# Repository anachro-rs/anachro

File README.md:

# Anachro Computer

**See [the documentation](https://anachro.computer) for more details!**

## Components

* [Anachro ICD](./crates/icd/README.md) - The Interface Control Document, containing protocol messages used between the Arbitrator/Client.
* [Client](./crates/client/README.md) - The Client Library, intended to run on each client
* [Server](./crates/server/README.md) - The Server/Broker library, intended to run on a single server

## Example Applications

* `client-tcp` - Example TCP Client
* `server-tcp` - Example TCP Server

# License

Licensed under either of

- Apache License, Version 2.0 ([LICENSE-APACHE](LICENSE-APACHE) or
  http://www.apache.org/licenses/LICENSE-2.0)

- MIT license ([LICENSE-MIT](LICENSE-MIT) or http://opensource.org/licenses/MIT)

at your option.

## Contribution

Unless you explicitly state otherwise, any contribution intentionally submitted
for inclusion in the work by you, as defined in the Apache-2.0 license, shall be
dual licensed as above, without any additional terms or conditions.

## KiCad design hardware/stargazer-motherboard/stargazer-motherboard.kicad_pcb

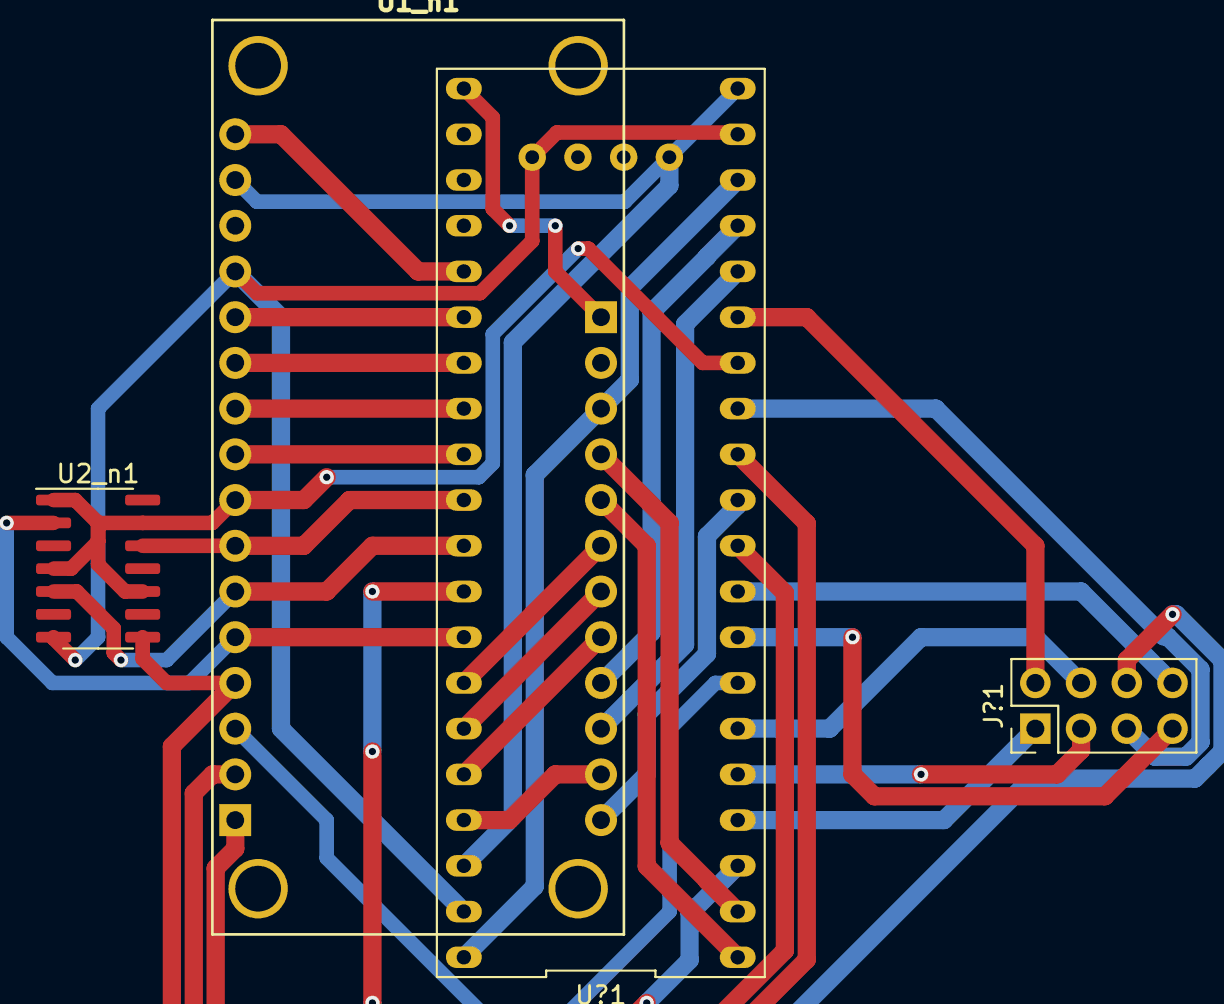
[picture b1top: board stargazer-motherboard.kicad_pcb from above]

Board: 2 copper layers, 4 parts (0 on the bottom side), 34 nets.

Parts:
J?1: black-pill-leftovers; PinHeader_2x04_P2.54mm_Vertical
U1_n1: ADAFRUIT_FEATHER
U2_n1: SN74LVC125AD; SOIC-14_3.9x8.7mm_P1.27mm
U?1: weact-black-pill; weact-blackpill

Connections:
/3v3_n: U1_n1.15, U?1.20, U?1.21, U?1.42
/A0_n: U1_n1.12, U?1.30
/A1_n: U1_n1.11, U?1.31
/A2_n: U1_n1.10, U?1.32
/A3_n: U1_n1.9, U?1.33
/AUX_n: U1_n1.1, U?1.3
/BP1_n: J?1.1, U?1.4
/BP2_n: J?1.2, U?1.15
/BP3_n: J?1.3, U?1.5
/BP4_n: J?1.4, U?1.6
/BP5_n: J?1.5, U?1.13
/BP6_n: J?1.6, U?1.36
/BP7_n: J?1.7, U?1.8
/BP8_n: J?1.8, U?1.9
/CARDn-CIPO: U1_n1.4, U2_n1.8, U?1.12
/CARDn-COPI: U1_n1.5, U2_n1.2, U?1.37
/CARDn-CSn: U1_n1.7, U2_n1.12, U?1.34
/CARDn-GO: U1_n1.8, U2_n1.1, U2_n1.4, U2_n1.10, U2_n1.13, U?1.14
/CARDn-SCK: U1_n1.6, U2_n1.5, U?1.35
/D0_n: U1_n1.3, U?1.7
/D1_n: U1_n1.2, U?1.10
/D2_n: U1_n1.28, U?1.11
/D3_n: U1_n1.27, U?1.41
/D5_n: U1_n1.26, U?1.16
/D6_n: U1_n1.25, U?1.17
/D9_n: U1_n1.24, U?1.40
/D10_n: U1_n1.23, U?1.39
/D11_n: U1_n1.22, U?1.38
/D12_n: U1_n1.21, U?1.1
/D13_n: U1_n1.20, U?1.2
/RSTn: U1_n1.16, U?1.29
/VBATn: U1_n1.17, U?1.25
/VBUSn: U1_n1.19, U?1.18, U?1.44
GND: U1_n1.13, U2_n1.7, U?1.19, U?1.24, U?1.43

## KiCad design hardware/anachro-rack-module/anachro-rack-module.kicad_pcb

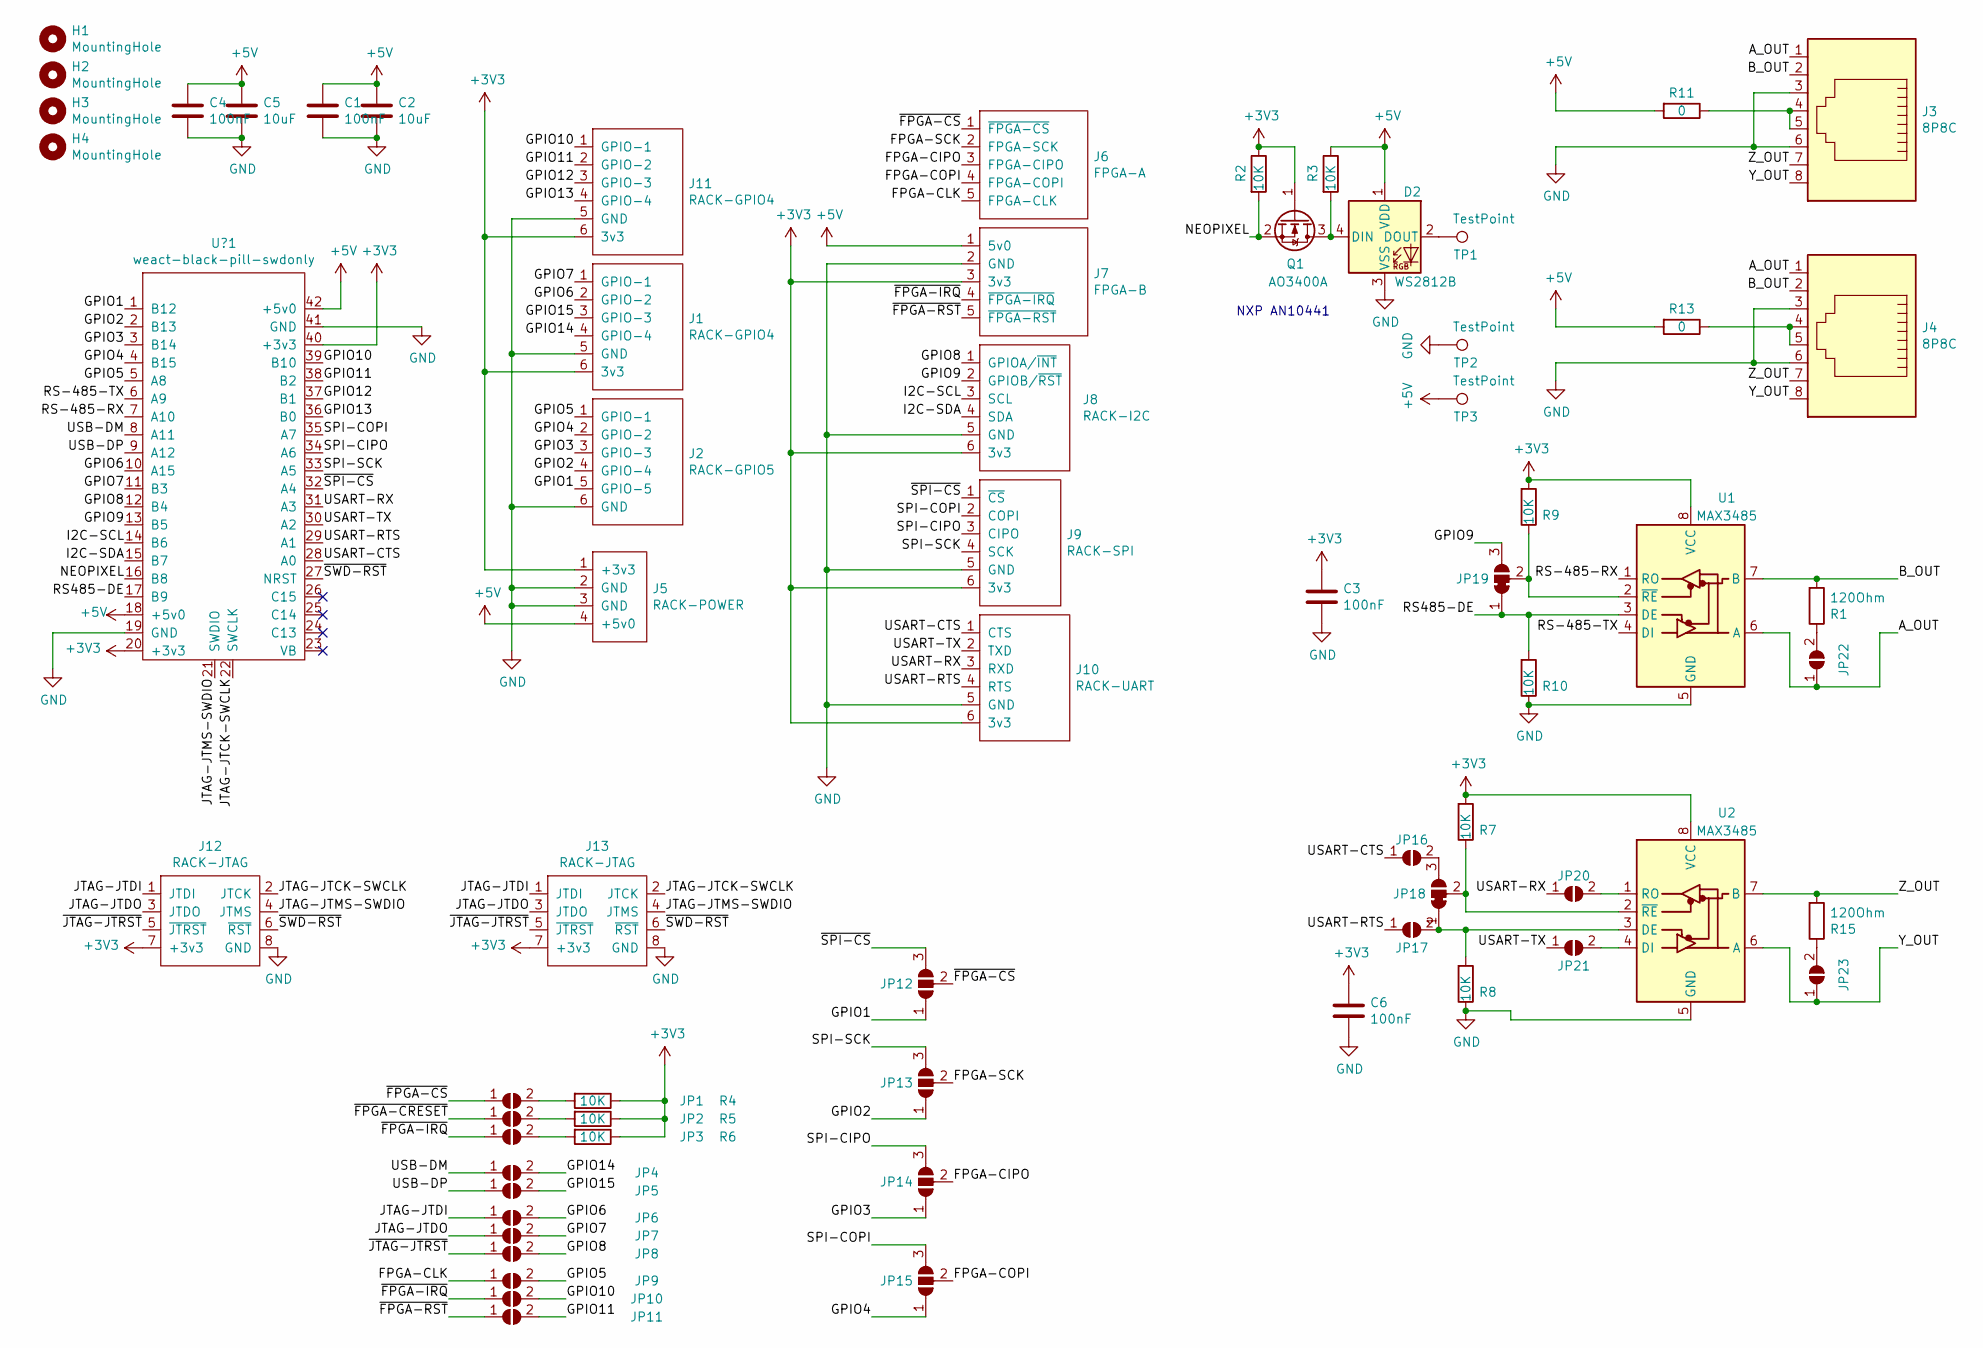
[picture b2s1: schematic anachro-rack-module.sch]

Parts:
C1, C3, C4, C6: 100nF; C_0805_2012Metric
C2, C5: 10uF; CP_Elec_4x5.3
D2: WS2812B; LED_WS2812B_PLCC4_5.0x5.0mm_P3.2mm
H1, H2, H3, H4: MountingHole; MountingHole_3.2mm_M3
J1, J11: RACK-GPIO4; PinHeader_1x06_P2.54mm_Vertical
J2: RACK-GPIO5; PinHeader_1x06_P2.54mm_Vertical
J3, J4: 8P8C; RJ45_Amphenol_54602-x08_Horizontal
J5: RACK-POWER; PinHeader_1x04_P2.54mm_Vertical
J6: FPGA-A; PinHeader_1x05_P2.54mm_Vertical
J7: FPGA-B; PinHeader_1x05_P2.54mm_Vertical
J8: RACK-I2C; PinHeader_1x06_P2.54mm_Vertical
J9: RACK-SPI; PinHeader_1x06_P2.54mm_Vertical
J10: RACK-UART; PinHeader_1x06_P2.54mm_Vertical
J12, J13: RACK-JTAG; PinHeader_2x04_P2.54mm_Vertical
JP1, JP2, JP3, JP4, JP5, JP6, JP7, JP8, JP9, JP10, JP11, JP16, JP17, JP20, JP21, JP22, JP23: SolderJumper_2_Open; SolderJumper-2_P1.3mm_Open_TrianglePad1.0x1.5mm
JP12, JP13, JP14, JP15: SolderJumper_3_Open; SolderJumper-3_P2.0mm_Open_TrianglePad1.0x1.5mm
JP18, JP19: SolderJumper_3_Bridged12; SolderJumper-3_P1.3mm_Bridged12_RoundedPad1.0x1.5mm_NumberL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
Q1: AO3400A; SOT-23
R1, R15: 120Ohm; R_0805_2012Metric
R2, R3, R4, R5, R6, R7, R8, R9, R10: 10K; R_0805_2012Metric
R11, R13: 0; R_0805_2012Metric
TP1, TP2, TP3: TestPoint; PinSocket_1x01_P2.54mm_Vertical
U1, U2: MAX3485; SOIC-8_3.9x4.9mm_P1.27mm
U?1: weact-black-pill-swdonly; weact-blackpill-swdonly

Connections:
/A_OUT: J3.1, J4.1, JP22.1 (A), U1.6 (A)
/B_OUT: J3.2, J4.2, R1.2, U1.7 (B)
/FPGA-CIPO: J6.3 (FPGA-CIPO), JP14.2 (C)
/FPGA-CLK: J6.5 (FPGA-CLK), JP9.1 (A)
/FPGA-COPI: J6.4 (FPGA-COPI), JP15.2 (C)
/FPGA-SCK: J6.2 (FPGA-SCK), JP13.2 (C)
/GPIO1: J2.5 (GPIO-5), JP12.1 (A), U?1.1 (B12)
/GPIO2: J2.4 (GPIO-4), JP13.1 (A), U?1.2 (B13)
/GPIO3: J2.3 (GPIO-3), JP14.1 (A), U?1.3 (B14)
/GPIO4: J2.2 (GPIO-2), JP15.1 (A), U?1.4 (B15)
/GPIO5: J2.1 (GPIO-1), JP9.2 (B), U?1.5 (A8)
/GPIO6: J1.2 (GPIO-2), JP6.2 (B), U?1.10 (A15)
/GPIO7: J1.1 (GPIO-1), JP7.2 (B), U?1.11 (B3)
/GPIO8: J8.1 (GPIOA/~INT), JP8.2 (B), U?1.12 (B4)
/GPIO9: J8.2 (GPIOB/~RST), JP19.3 (B), U?1.13 (B5)
/GPIO10: J11.1 (GPIO-1), JP10.2 (B), U?1.39 (B10)
/GPIO11: J11.2 (GPIO-2), JP11.2 (B), U?1.38 (B2)
/GPIO12: J11.3 (GPIO-3), U?1.37 (B1)
/GPIO13: J11.4 (GPIO-4), U?1.36 (B0)
/GPIO14: J1.4 (GPIO-4), JP4.2 (B)
/GPIO15: J1.3 (GPIO-3), JP5.2 (B)
/I2C-SCL: J8.3 (SCL), U?1.14 (B6)
/I2C-SDA: J8.4 (SDA), U?1.15 (B7)
/JTAG-JTCK-SWCLK: J12.2 (JTCK), J13.2 (JTCK), U?1.22 (SWCLK)
/JTAG-JTDI: J12.1 (JTDI), J13.1 (JTDI), JP6.1 (A)
/JTAG-JTDO: J12.3 (JTDO), J13.3 (JTDO), JP7.1 (A)
/JTAG-JTMS-SWDIO: J12.4 (JTMS), J13.4 (JTMS), U?1.21 (SWDIO)
/NEOPIXEL: Q1.2 (S), R2.2, U?1.16 (B8)
/RS485-DE: JP19.1 (A), R10.2, U1.3 (DE), U?1.17 (B9)
/RS-485-RX: U1.1 (RO), U?1.7 (A10)
/RS-485-TX: U1.4 (DI), U?1.6 (A9)
/SPI-CIPO: J9.3 (CIPO), JP14.3 (B), U?1.34 (A6)
/SPI-COPI: J9.2 (COPI), JP15.3 (B), U?1.35 (A7)
/SPI-SCK: J9.4 (SCK), JP13.3 (B), U?1.33 (A5)
/USART-CTS: J10.1 (CTS), JP16.1 (A), U?1.28 (A0)
/USART-RTS: J10.4 (RTS), JP17.1 (A), U?1.29 (A1)
/USART-RX: J10.3 (RXD), JP20.1 (A), U?1.31 (A3)
/USART-TX: J10.2 (TXD), JP21.1 (A), U?1.30 (A2)
/USB-DM: JP4.1 (A), U?1.8 (A11)
/USB-DP: JP5.1 (A), U?1.9 (A12)
/Y_OUT: J3.8, J4.8, JP23.1 (A), U2.6 (A)
/Z_OUT: J3.7, J4.7, R15.2, U2.7 (B)
/~FPGA-CRESET: JP2.1 (A)
/~FPGA-CS: J6.1 (~FPGA-CS), JP1.1 (A), JP12.2 (C)
/~FPGA-IRQ: J7.4 (~FPGA-IRQ), JP3.1 (A), JP10.1 (A)
/~FPGA-RST: J7.5 (~FPGA-RST), JP11.1 (A)
/~JTAG-JTRST: J12.5 (~JTRST), J13.5 (~JTRST), JP8.1 (A)
/~SPI-CS: J9.1 (~CS), JP12.3 (B), U?1.32 (A4)
/~SWD-RST: J12.6 (~RST), J13.6 (~RST), U?1.27 (NRST)
GND: C1.2, C2.2, C3.2, C4.2, C5.2, C6.2, D2.3 (VSS), J1.5 (GND), J2.6 (GND), J3.3, J3.6, J4.3, J4.6, J5.2 (GND), J5.3 (GND), J7.2 (GND), J8.5 (GND), J9.5 (GND), J10.5 (GND), J11.5 (GND), J12.8 (GND), J13.8 (GND), R8.1, R10.1, TP2.1, U1.5 (GND), U2.5 (GND), U?1.19 (GND), U?1.41 (GND)
unnamed: D2.2 (DOUT), TP1.1
unnamed: D2.4 (DIN), Q1.3 (D), R3.2
unnamed: J3.4, J3.5, R11.1
unnamed: J4.4, J4.5, R13.1
unnamed: JP1.2 (B), R4.2
unnamed: JP2.2 (B), R5.2
unnamed: JP3.2 (B), R6.2
unnamed: JP16.2 (B), JP18.3 (B)
unnamed: JP17.2 (B), JP18.1 (A), R8.2, U2.3 (DE)
unnamed: JP18.2 (C), R7.1, U2.2 (~RE)
unnamed: JP19.2 (C), R9.1, U1.2 (~RE)
unnamed: JP20.2 (B), U2.1 (RO)
unnamed: JP21.2 (B), U2.4 (DI)
unnamed: JP22.2 (B), R1.1
unnamed: JP23.2 (B), R15.1

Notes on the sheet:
NXP AN10441

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
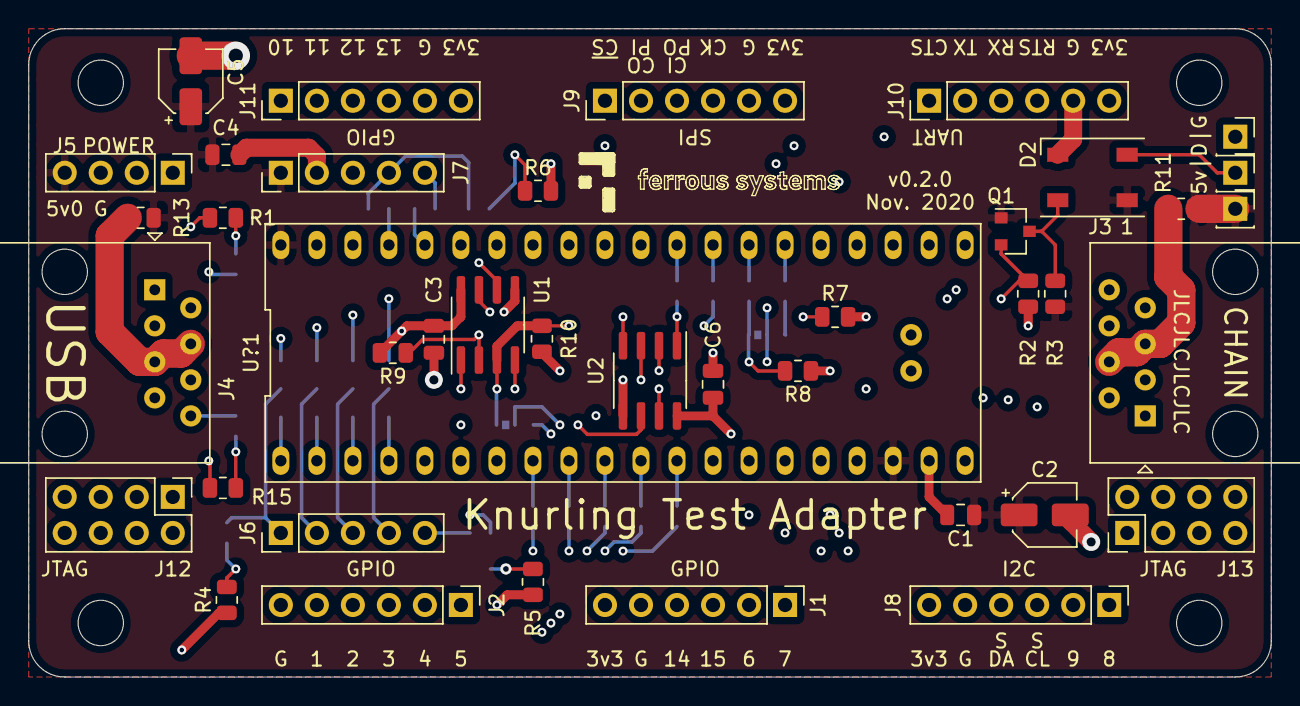
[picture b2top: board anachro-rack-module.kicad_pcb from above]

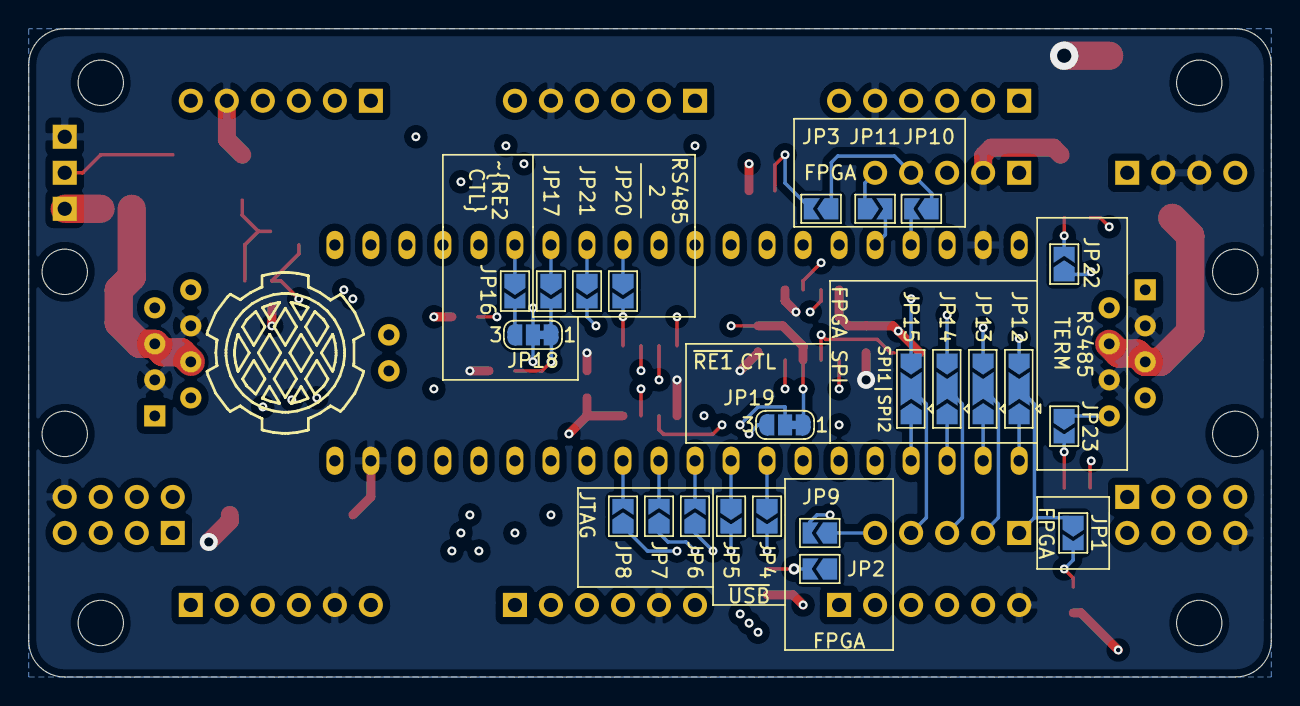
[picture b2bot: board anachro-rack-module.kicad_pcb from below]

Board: 4 copper layers, 87.6 x 45.7 mm, 67 parts (23 on the bottom side), 66 nets.

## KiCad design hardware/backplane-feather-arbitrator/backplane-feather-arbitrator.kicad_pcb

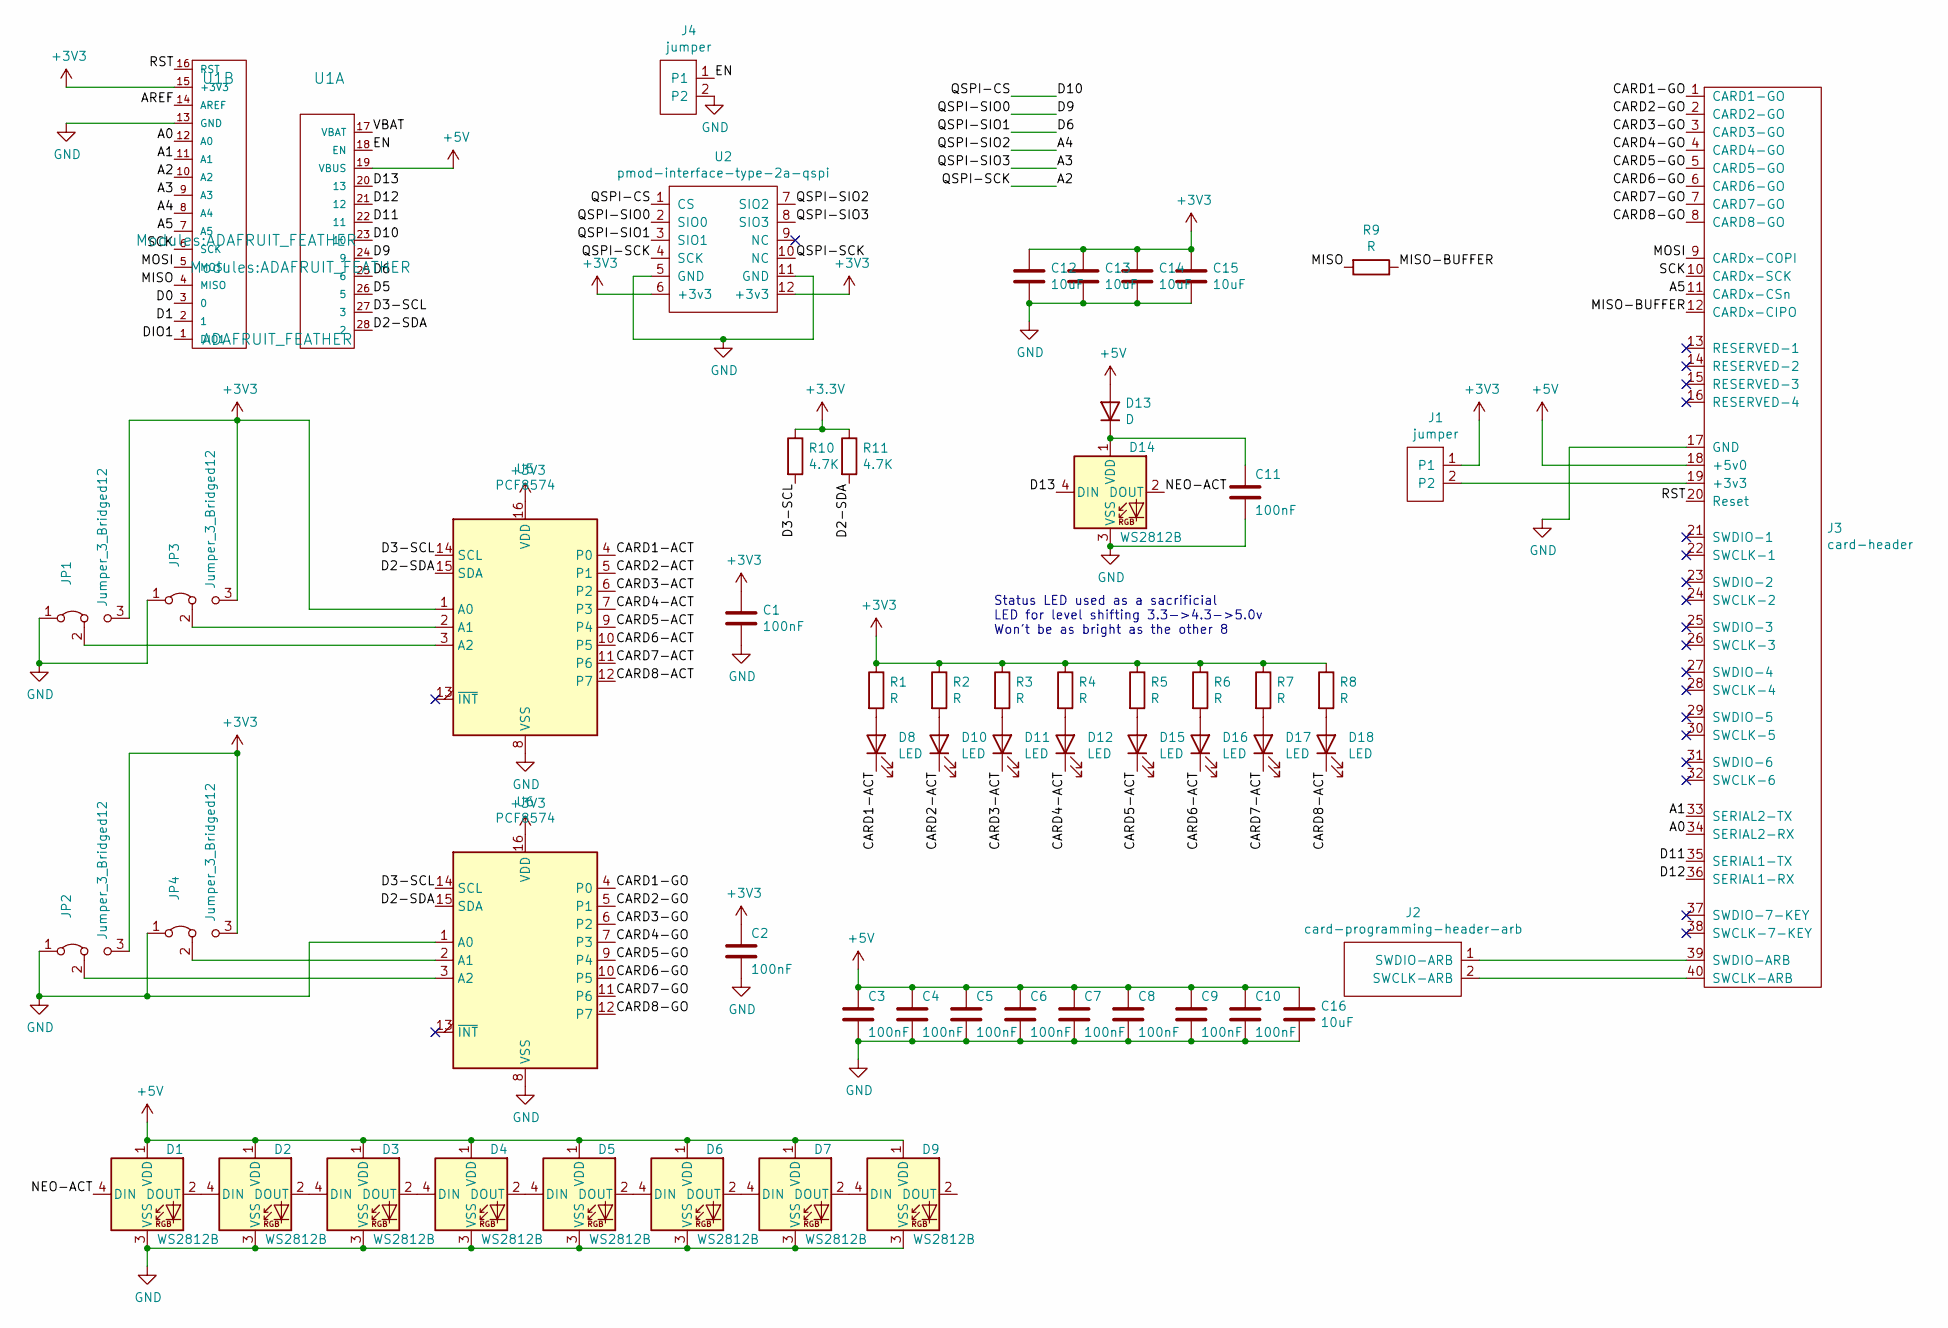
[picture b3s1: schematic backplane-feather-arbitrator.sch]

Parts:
C1, C2, C3, C4, C5, C6, C7, C8, C9, C10, C11: 100nF; C_0805_2012Metric
C12, C13, C14, C15, C16: 10uF; CP_Elec_4x5.3
D1, D2, D3, D4, D5, D6, D7, D9, D14: WS2812B; LED_WS2812B_PLCC4_5.0x5.0mm_P3.2mm
D8, D10, D11, D12, D15, D16, D17, D18: LED; LED_0805_2012Metric
D13: D; D_SOD-123
J1, J4: jumper; PinHeader_1x02_P2.54mm_Vertical
J2: card-programming-header-arb; PinHeader_1x02_P2.54mm_Vertical
J3: card-header; PinHeader_1x40_P2.54mm_Horizontal
JP1, JP2, JP3, JP4: Jumper_3_Bridged12; SolderJumper-3_P1.3mm_Bridged12_RoundedPad1.0x1.5mm
R1, R2, R3, R4, R5, R6, R7, R8, R9: R; R_0805_2012Metric
R10, R11: 4.7K; R_0805_2012Metric
U1: ADAFRUIT_FEATHER
U2: pmod-interface-type-2a-qspi; pmod-double
U5, U6: PCF8574; SOIC127P1032X265-16N

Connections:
+5V: C3.1, C4.1, C5.1, C6.1, C7.1, C8.1, C9.1, C10.1, C16.1, D1.1 (VDD), D2.1 (VDD), D3.1 (VDD), D4.1 (VDD), D5.1 (VDD), D6.1 (VDD), D7.1 (VDD), D9.1 (VDD), D13.2 (A), J3.18 (+5v0), U1.19 (VBUS)
/A0: J3.34 (SERIAL2-RX), U1.12 (A0)
/A1: J3.33 (SERIAL2-TX), U1.11 (A1)
/A2: U1.10 (A2), U2.4 (SCK), U2.10 (NC)
/A3: U1.9 (A3), U2.8 (SIO3)
/A4: U1.8 (A4), U2.7 (SIO2)
/A5: J3.11 (CARDx-CSn), U1.7 (A5)
/AREF: U1.14 (AREF)
/CARD1-ACT: D8.1 (K), U5.4 (P0)
/CARD1-GO: J3.1 (CARD1-GO), U6.4 (P0)
/CARD2-ACT: D10.1 (K), U5.5 (P1)
/CARD2-GO: J3.2 (CARD2-GO), U6.5 (P1)
/CARD3-ACT: D11.1 (K), U5.6 (P2)
/CARD3-GO: J3.3 (CARD3-GO), U6.6 (P2)
/CARD4-ACT: D12.1 (K), U5.7 (P3)
/CARD4-GO: J3.4 (CARD4-GO), U6.7 (P3)
/CARD5-ACT: D15.1 (K), U5.9 (P4)
/CARD5-GO: J3.5 (CARD5-GO), U6.9 (P4)
/CARD6-ACT: D16.1 (K), U5.10 (P5)
/CARD6-GO: J3.6 (CARD6-GO), U6.10 (P5)
/CARD7-ACT: D17.1 (K), U5.11 (P6)
/CARD7-GO: J3.7 (CARD7-GO), U6.11 (P6)
/CARD8-ACT: D18.1 (K), U5.12 (P7)
/CARD8-GO: J3.8 (CARD8-GO), U6.12 (P7)
/D0: U1.3 (0)
/D1: U1.2 (1)
/D2-SDA: R11.2, U1.28 (2), U5.15 (SDA), U6.15 (SDA)
/D3-SCL: R10.2, U1.27 (3), U5.14 (SCL), U6.14 (SCL)
/D5: U1.26 (5)
/D6: U1.25 (6), U2.3 (SIO1)
/D9: U1.24 (9), U2.2 (SIO0)
/D10: U1.23 (10), U2.1 (CS)
/D11: J3.35 (SERIAL1-TX), U1.22 (11)
/D12: J3.36 (SERIAL1-RX), U1.21 (12)
/D13: D14.4 (DIN), U1.20 (13)
/DIO1: U1.1 (DIO1)
/EN: J4.1, U1.18 (EN)
/MISO: R9.2, U1.4 (MISO)
/MISO-BUFFER: J3.12 (CARDx-CIPO), R9.1
/MOSI: J3.9 (CARDx-COPI), U1.5 (MOSI)
/NEO-ACT: D1.4 (DIN), D14.2 (DOUT)
/RST: J3.20 (Reset), U1.16 (RST)
/SCK: J3.10 (CARDx-SCK), U1.6 (SCK)
/VBAT: U1.17 (VBAT)
GND: C1.2, C2.2, C3.2, C4.2, C5.2, C6.2, C7.2, C8.2, C9.2, C10.2, C11.2, C12.2, C13.2, C14.2, C15.2, C16.2, D1.3 (VSS), D2.3 (VSS), D3.3 (VSS), D4.3 (VSS), D5.3 (VSS), D6.3 (VSS), D7.3 (VSS), D9.3 (VSS), D14.3 (VSS), J3.17 (GND), J4.2, JP1.1 (A), JP2.1 (A), JP3.1 (A), JP4.1 (A), U1.13 (GND), U2.5 (GND), U2.11 (GND), U5.8 (VSS), U6.1 (A0), U6.8 (VSS)
unnamed: C11.1, D13.1 (K), D14.1 (VDD)
unnamed: D1.2 (DOUT), D2.4 (DIN)
unnamed: D2.2 (DOUT), D3.4 (DIN)
unnamed: D3.2 (DOUT), D4.4 (DIN)
unnamed: D4.2 (DOUT), D5.4 (DIN)
unnamed: D5.2 (DOUT), D6.4 (DIN)
unnamed: D6.2 (DOUT), D7.4 (DIN)
unnamed: D7.2 (DOUT), D9.4 (DIN)
unnamed: D8.2 (A), R1.2
unnamed: D10.2 (A), R2.2
unnamed: D11.2 (A), R3.2
unnamed: D12.2 (A), R4.2
unnamed: D15.2 (A), R5.2
unnamed: D16.2 (A), R6.2
unnamed: D17.2 (A), R7.2
unnamed: D18.2 (A), R8.2
unnamed: J1.2, J3.19 (+3v3)
unnamed: J2.1 (SWDIO-ARB), J3.39 (SWDIO-ARB)
unnamed: J2.2 (SWCLK-ARB), J3.40 (SWCLK-ARB)
unnamed: JP1.2 (C), U5.3 (A2)
unnamed: JP2.2 (C), U6.3 (A2)
unnamed: JP3.2 (C), U5.2 (A1)
unnamed: JP4.2 (C), U6.2 (A1)

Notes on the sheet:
Status LED used as a sacrificial LED for level shifting 3.3->4.3->5.0v Won't be as bright as the other 8

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
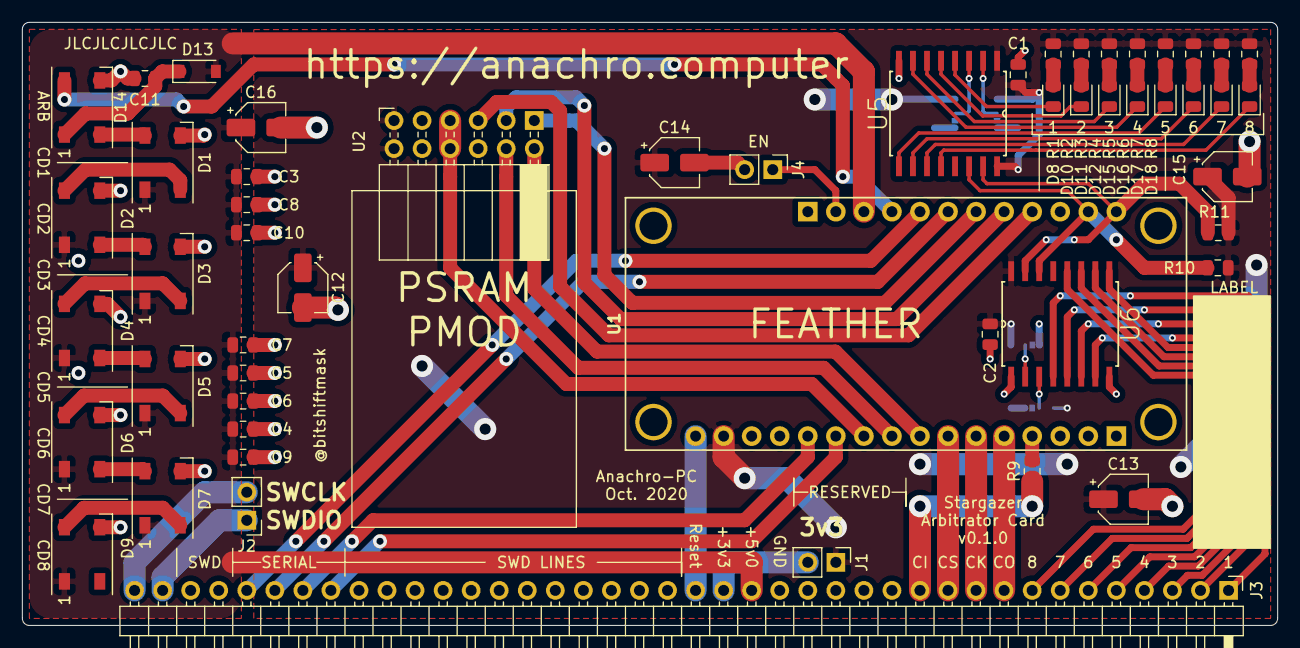
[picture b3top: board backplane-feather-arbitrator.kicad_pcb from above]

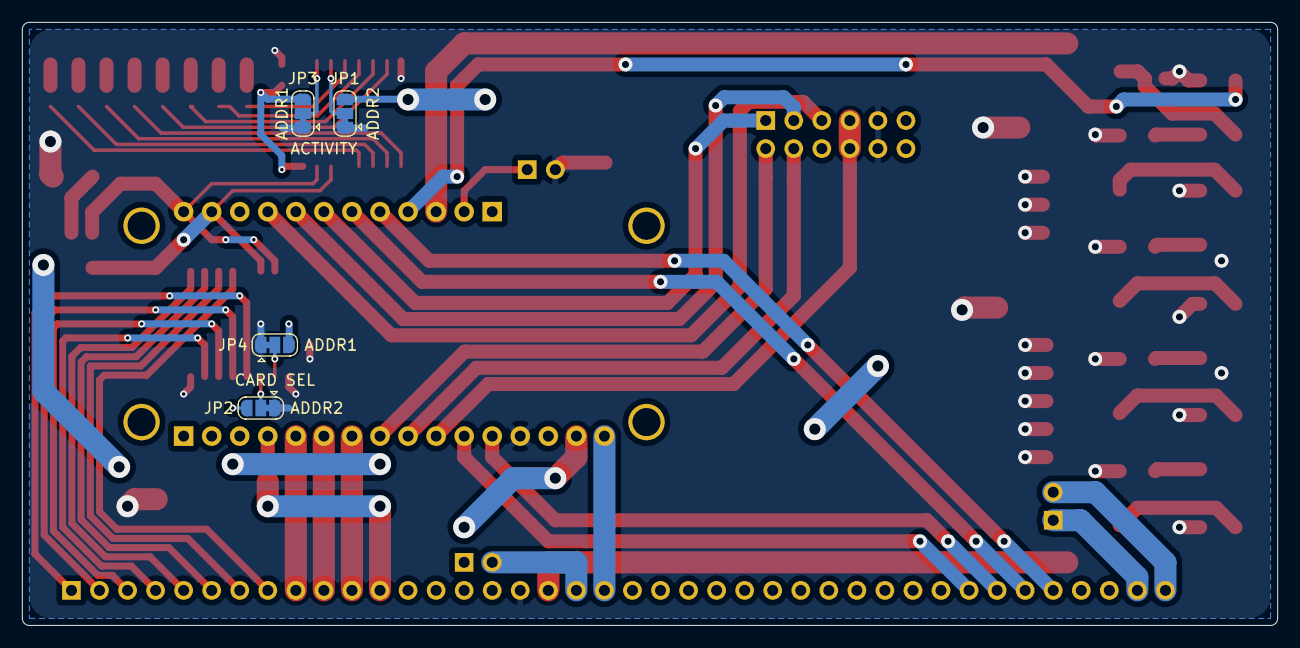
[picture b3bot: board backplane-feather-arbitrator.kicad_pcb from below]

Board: 2 copper layers, 113.7 x 54.6 mm, 57 parts (4 on the bottom side), 63 nets.

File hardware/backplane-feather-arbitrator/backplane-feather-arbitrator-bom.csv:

Reference, Quantity, Value, Footprint, Datasheet
C1 C3 C10 C4 C5 C6 C7 C8 C9 C2 C11 ,11,"100nF","Capacitor_SMD:C_0805_2012Metric","~"
C12 C13 C14 C15 C16 ,5,"10uF","Capacitor_SMD:CP_Elec_4x5.3","~"
D1 D2 D3 D4 D5 D6 D7 D9 D14 ,9,"WS2812B","LED_SMD:LED_WS2812B_PLCC4_5.0x5.0mm_P3.2mm","https://cdn-shop.adafruit.com/datasheets/WS2812B.pdf"
D13 ,1,"D","Diode_SMD:D_0805_2012Metric","~"
D8 D10 D11 D12 D15 D16 D17 D18 ,8,"LED","LED_SMD:LED_0805_2012Metric","~"
J1 J4 ,2,"jumper","Connector_PinHeader_2.54mm:PinHeader_1x02_P2.54mm_Vertical",""
J2 ,1,"card-programming-header-arb","Connector_PinHeader_2.54mm:PinHeader_1x02_P2.54mm_Vertical",""
J3 ,1,"card-header","Connector_PinHeader_2.54mm:PinHeader_1x40_P2.54mm_Horizontal",""
JP4 JP2 JP3 JP1 ,4,"Jumper_3_Bridged12","Jumper:SolderJumper-3_P1.3mm_Bridged12_RoundedPad1.0x1.5mm","~"
R1 R9 R2 R3 R4 R5 R6 R7 R8 ,9,"R","Resistor_SMD:R_0805_2012Metric","~"
R10 R11 ,2,"4.7K","Resistor_SMD:R_0805_2012Metric","~"
U1 ,1,"ADAFRUIT_FEATHER","Modules:ADAFRUIT_FEATHER",""
U2 ,1,"pmod-interface-type-2a-qspi","stargazer-stalk:pmod-double",""
U6 U5 ,2,"PCF8574","stargazer-stalk:SOIC127P1032X265-16N","http://www.nxp.com/documents/data_sheet/PCF8574_PCF8574A.pdf"

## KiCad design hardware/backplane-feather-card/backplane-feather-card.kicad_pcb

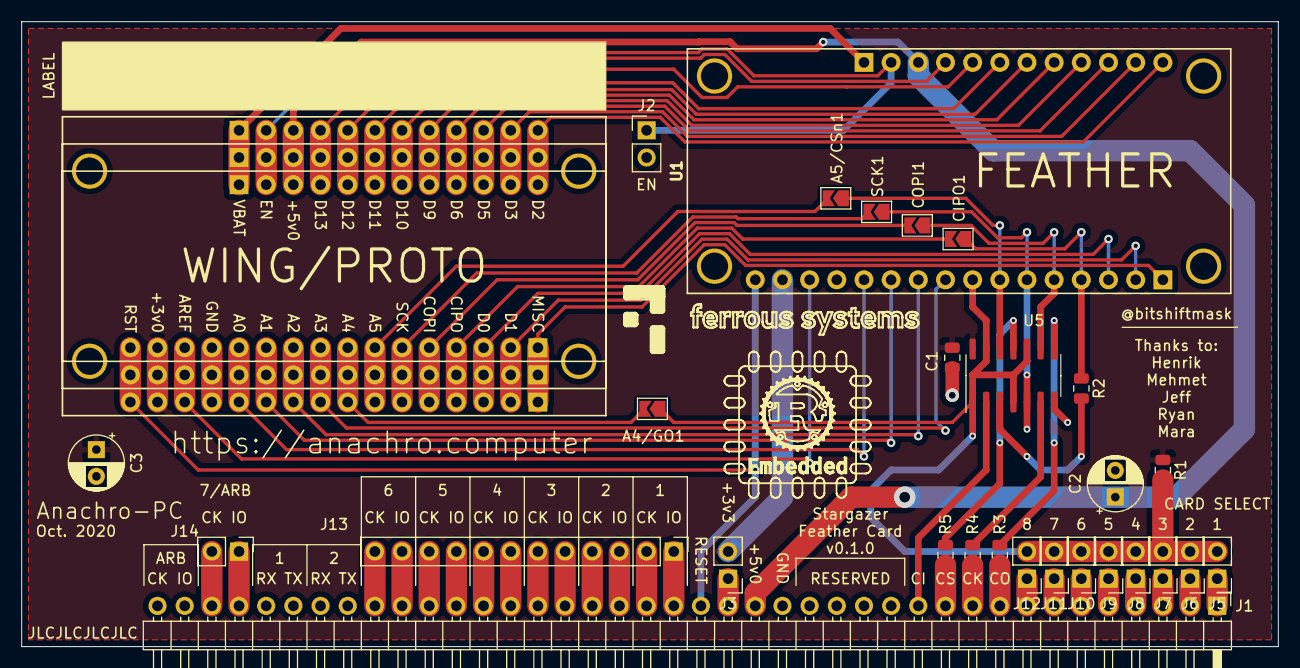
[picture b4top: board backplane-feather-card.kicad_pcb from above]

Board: 2 copper layers, 117.5 x 58.4 mm, 31 parts (0 on the bottom side), 64 nets.

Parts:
A4/GO1, A5/CSn1: SolderJumper_2_Open; SolderJumper-2_P1.3mm_Open_TrianglePad1.0x1.5mm
C1: 0.1uF; C_0805_2012Metric
C2, C3: 1uF; CP_Radial_D5.0mm_P2.50mm
CIPO1: SolderJumper_2_Open; SolderJumper-2_P1.3mm_Open_TrianglePad1.0x1.5mm
COPI1: SolderJumper_2_Open; SolderJumper-2_P1.3mm_Open_TrianglePad1.0x1.5mm
J1: card-header; PinHeader_1x40_P2.54mm_Horizontal
J2, J3, J5, J6, J7, J8, J9, J10, J11, J12: jumper; PinHeader_1x02_P2.54mm_Vertical
J13: card-programming-header-a; PinHeader_1x12_P2.54mm_Vertical
J14: card-programming-header-b; PinHeader_1x02_P2.54mm_Vertical
R1: 10k; R_0805_2012Metric
R2, R3, R4, R5: 50 Ohm; R_0805_2012Metric
SCK1: SolderJumper_2_Open; SolderJumper-2_P1.3mm_Open_TrianglePad1.0x1.5mm
U1, U4: ADAFRUIT_FEATHER
U2, U3: ADAFRUIT_FEATHER; ADAFRUIT_FEATHER_NOHOLES
U5: SN74LVC125AD; SOIC-14_3.9x8.7mm_P1.27mm

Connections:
+3V3: C1.1, C3.1, J3.2, R1.1, U1.15, U2.15, U3.15, U4.15, U5.14
+5V: C2.1, J1.18, U1.19, U2.19, U3.19, U4.19
/+3v3-backplane: J1.19, J3.1
/CIPO: J1.12, U5.2
/CIPO-BUFFER: R2.2, U5.3
/CIPO-FEATHER: CIPO1.1, R2.1, U1.4
/COPI: J1.9, R3.1
/COPI-BUFFER: R3.2, U5.8
/COPI-FEATHER: COPI1.1, U1.5, U5.9
/CSn: J1.11, R5.1
/CSn-BUFFER: R5.2, U5.11
/CSn-FEATHER: A5/CSn1.1, U1.7, U5.12
/GO: A4/GO1.1, J5.2, J6.2, J7.2, J8.2, J9.2, J10.2, J11.2, J12.2, R1.2, U1.8, U5.1, U5.4, U5.10, U5.13
/Reset: J1.20, U1.16, U2.16, U3.16, U4.16
/SCK: J1.10, R4.1
/SCK-BUFFER: R4.2, U5.6
/SCK-FEATHER: SCK1.1, U1.6, U5.5
/debug-headers/A0: U1.12, U2.12, U3.12, U4.12
/debug-headers/A1: U1.11, U2.11, U3.11, U4.11
/debug-headers/A2: U1.10, U2.10, U3.10, U4.10
/debug-headers/A3: U1.9, U2.9, U3.9, U4.9
/debug-headers/A4: A4/GO1.2, U2.8, U3.8, U4.8
/debug-headers/A5: A5/CSn1.2, U2.7, U3.7, U4.7
/debug-headers/AREF: U1.14, U2.14, U3.14, U4.14
/debug-headers/D0: U1.3, U2.3, U3.3, U4.3
/debug-headers/D1: U1.2, U2.2, U3.2, U4.2
/debug-headers/D2: U1.28, U2.28, U3.28, U4.28
/debug-headers/D3: U1.27, U2.27, U3.27, U4.27
/debug-headers/D5: U1.26, U2.26, U3.26, U4.26
/debug-headers/D6: U1.25, U2.25, U3.25, U4.25
/debug-headers/D9: U1.24, U2.24, U3.24, U4.24
/debug-headers/D10: U1.23, U2.23, U3.23, U4.23
/debug-headers/D11: U1.22, U2.22, U3.22, U4.22
/debug-headers/D12: U1.21, U2.21, U3.21, U4.21
/debug-headers/D13: U1.20, U2.20, U3.20, U4.20
/debug-headers/DIO1: U1.1, U2.1, U3.1, U4.1
/debug-headers/EN: J2.1, U1.18, U2.18, U3.18, U4.18
/debug-headers/MISO: CIPO1.2, U2.4, U3.4, U4.4
/debug-headers/MOSI: COPI1.2, U2.5, U3.5, U4.5
/debug-headers/SCK: SCK1.2, U2.6, U3.6, U4.6
/debug-headers/VBAT: U1.17, U2.17, U3.17, U4.17
/go-jumpers/CARD1-GO: J1.1, J5.1
/go-jumpers/CARD2-GO: J1.2, J6.1
/go-jumpers/CARD3-GO: J1.3, J7.1
/go-jumpers/CARD4-GO: J1.4, J8.1
/go-jumpers/CARD5-GO: J1.5, J9.1
/go-jumpers/CARD6-GO: J1.6, J10.1
/go-jumpers/CARD7-GO: J1.7, J11.1
/go-jumpers/CARD8-GO: J1.8, J12.1
GND: C1.2, C2.2, C3.2, J1.17, J2.2, U1.13, U2.13, U3.13, U4.13, U5.7
unnamed: J1.21, J13.1
unnamed: J1.22, J13.2
unnamed: J1.23, J13.3
unnamed: J1.24, J13.4
unnamed: J1.25, J13.5
unnamed: J1.26, J13.6
unnamed: J1.27, J13.7
unnamed: J1.28, J13.8
unnamed: J1.29, J13.9
unnamed: J1.30, J13.10
unnamed: J1.31, J13.11
unnamed: J1.32, J13.12
unnamed: J1.37, J14.1
unnamed: J1.38, J14.2

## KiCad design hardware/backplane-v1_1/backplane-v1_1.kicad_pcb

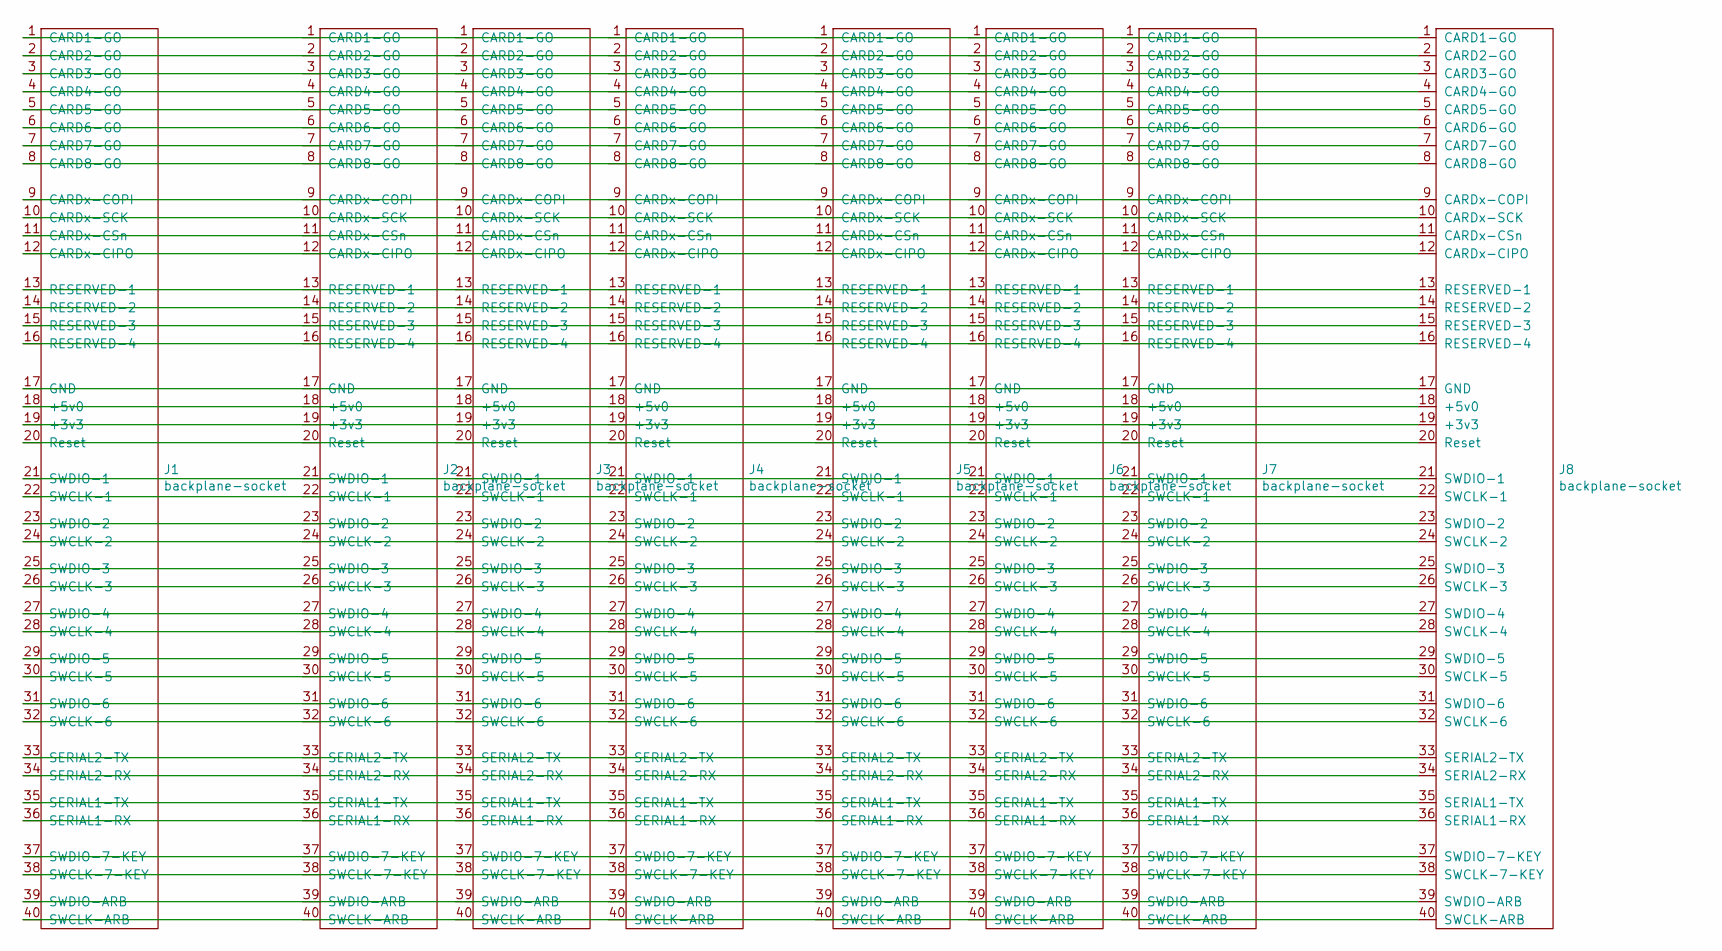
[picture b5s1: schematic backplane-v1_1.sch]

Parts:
J1, J2, J3, J4, J5, J6, J7, J8: backplane-socket; PinSocket_1x40_P2.54mm_Vertical

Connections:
unnamed: J1.1 (CARD1-GO), J8.1 (CARD1-GO)
unnamed: J1.2 (CARD2-GO), J8.2 (CARD2-GO)
unnamed: J1.3 (CARD3-GO), J8.3 (CARD3-GO)
unnamed: J1.4 (CARD4-GO), J8.4 (CARD4-GO)
unnamed: J1.5 (CARD5-GO), J8.5 (CARD5-GO)
unnamed: J1.6 (CARD6-GO), J8.6 (CARD6-GO)
unnamed: J1.7 (CARD7-GO), J8.7 (CARD7-GO)
unnamed: J1.8 (CARD8-GO), J8.8 (CARD8-GO)
unnamed: J1.9 (CARDx-COPI), J8.9 (CARDx-COPI)
unnamed: J1.10 (CARDx-SCK), J8.10 (CARDx-SCK)
unnamed: J1.11 (CARDx-CSn), J8.11 (CARDx-CSn)
unnamed: J1.12 (CARDx-CIPO), J8.12 (CARDx-CIPO)
unnamed: J1.13 (RESERVED-1), J8.13 (RESERVED-1)
unnamed: J1.14 (RESERVED-2), J8.14 (RESERVED-2)
unnamed: J1.15 (RESERVED-3), J8.15 (RESERVED-3)
unnamed: J1.16 (RESERVED-4), J8.16 (RESERVED-4)
unnamed: J1.17 (GND), J8.17 (GND)
unnamed: J1.18 (+5v0), J8.18 (+5v0)
unnamed: J1.19 (+3v3), J8.19 (+3v3)
unnamed: J1.20 (Reset), J8.20 (Reset)
unnamed: J1.21 (SWDIO-1), J8.21 (SWDIO-1)
unnamed: J1.22 (SWCLK-1), J8.22 (SWCLK-1)
unnamed: J1.23 (SWDIO-2), J8.23 (SWDIO-2)
unnamed: J1.24 (SWCLK-2), J8.24 (SWCLK-2)
unnamed: J1.25 (SWDIO-3), J8.25 (SWDIO-3)
unnamed: J1.26 (SWCLK-3), J8.26 (SWCLK-3)
unnamed: J1.27 (SWDIO-4), J8.27 (SWDIO-4)
unnamed: J1.28 (SWCLK-4), J8.28 (SWCLK-4)
unnamed: J1.29 (SWDIO-5), J8.29 (SWDIO-5)
unnamed: J1.30 (SWCLK-5), J8.30 (SWCLK-5)
unnamed: J1.31 (SWDIO-6), J8.31 (SWDIO-6)
unnamed: J1.32 (SWCLK-6), J8.32 (SWCLK-6)
unnamed: J1.33 (SERIAL2-TX), J8.33 (SERIAL2-TX)
unnamed: J1.34 (SERIAL2-RX), J8.34 (SERIAL2-RX)
unnamed: J1.35 (SERIAL1-TX), J8.35 (SERIAL1-TX)
unnamed: J1.36 (SERIAL1-RX), J8.36 (SERIAL1-RX)
unnamed: J1.37 (SWDIO-7-KEY), J8.37 (SWDIO-7-KEY)
unnamed: J1.38 (SWCLK-7-KEY), J8.38 (SWCLK-7-KEY)
unnamed: J1.39 (SWDIO-ARB), J8.39 (SWDIO-ARB)
unnamed: J1.40 (SWCLK-ARB), J8.40 (SWCLK-ARB)
